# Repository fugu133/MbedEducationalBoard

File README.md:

# Mbed Educational Board
マイコン教育用として開発した基板になります．  
ベースは[mbed LPC1768](https://os.mbed.com/platforms/mbed-LPC1768/)でmbed OSを使ってプロトタイピング開発が可能です.  

サイズが75mm x 55mmの基板に以下の機能が搭載されています．
* タクトスイッチ x4
* アナログボリューム x3
* 完全絶縁のモータドライバ x2
* 6軸IMUセンサ x1
* トランスデューサ x1
* USBコネクタ x1
* GPIO x5 (内2つはI2C)

初学者向けに周辺機器を動かすための[ドライバ](https://github.com/fugu133/MbedEducationalBoard/tree/main/mbed/flib)を用意しているので簡単に扱えるかと思います．

比較的簡単にはんだ付けができるよう一部モジュール基板を使用しています．  
この基板一枚で簡単なロボットも作ることができます！

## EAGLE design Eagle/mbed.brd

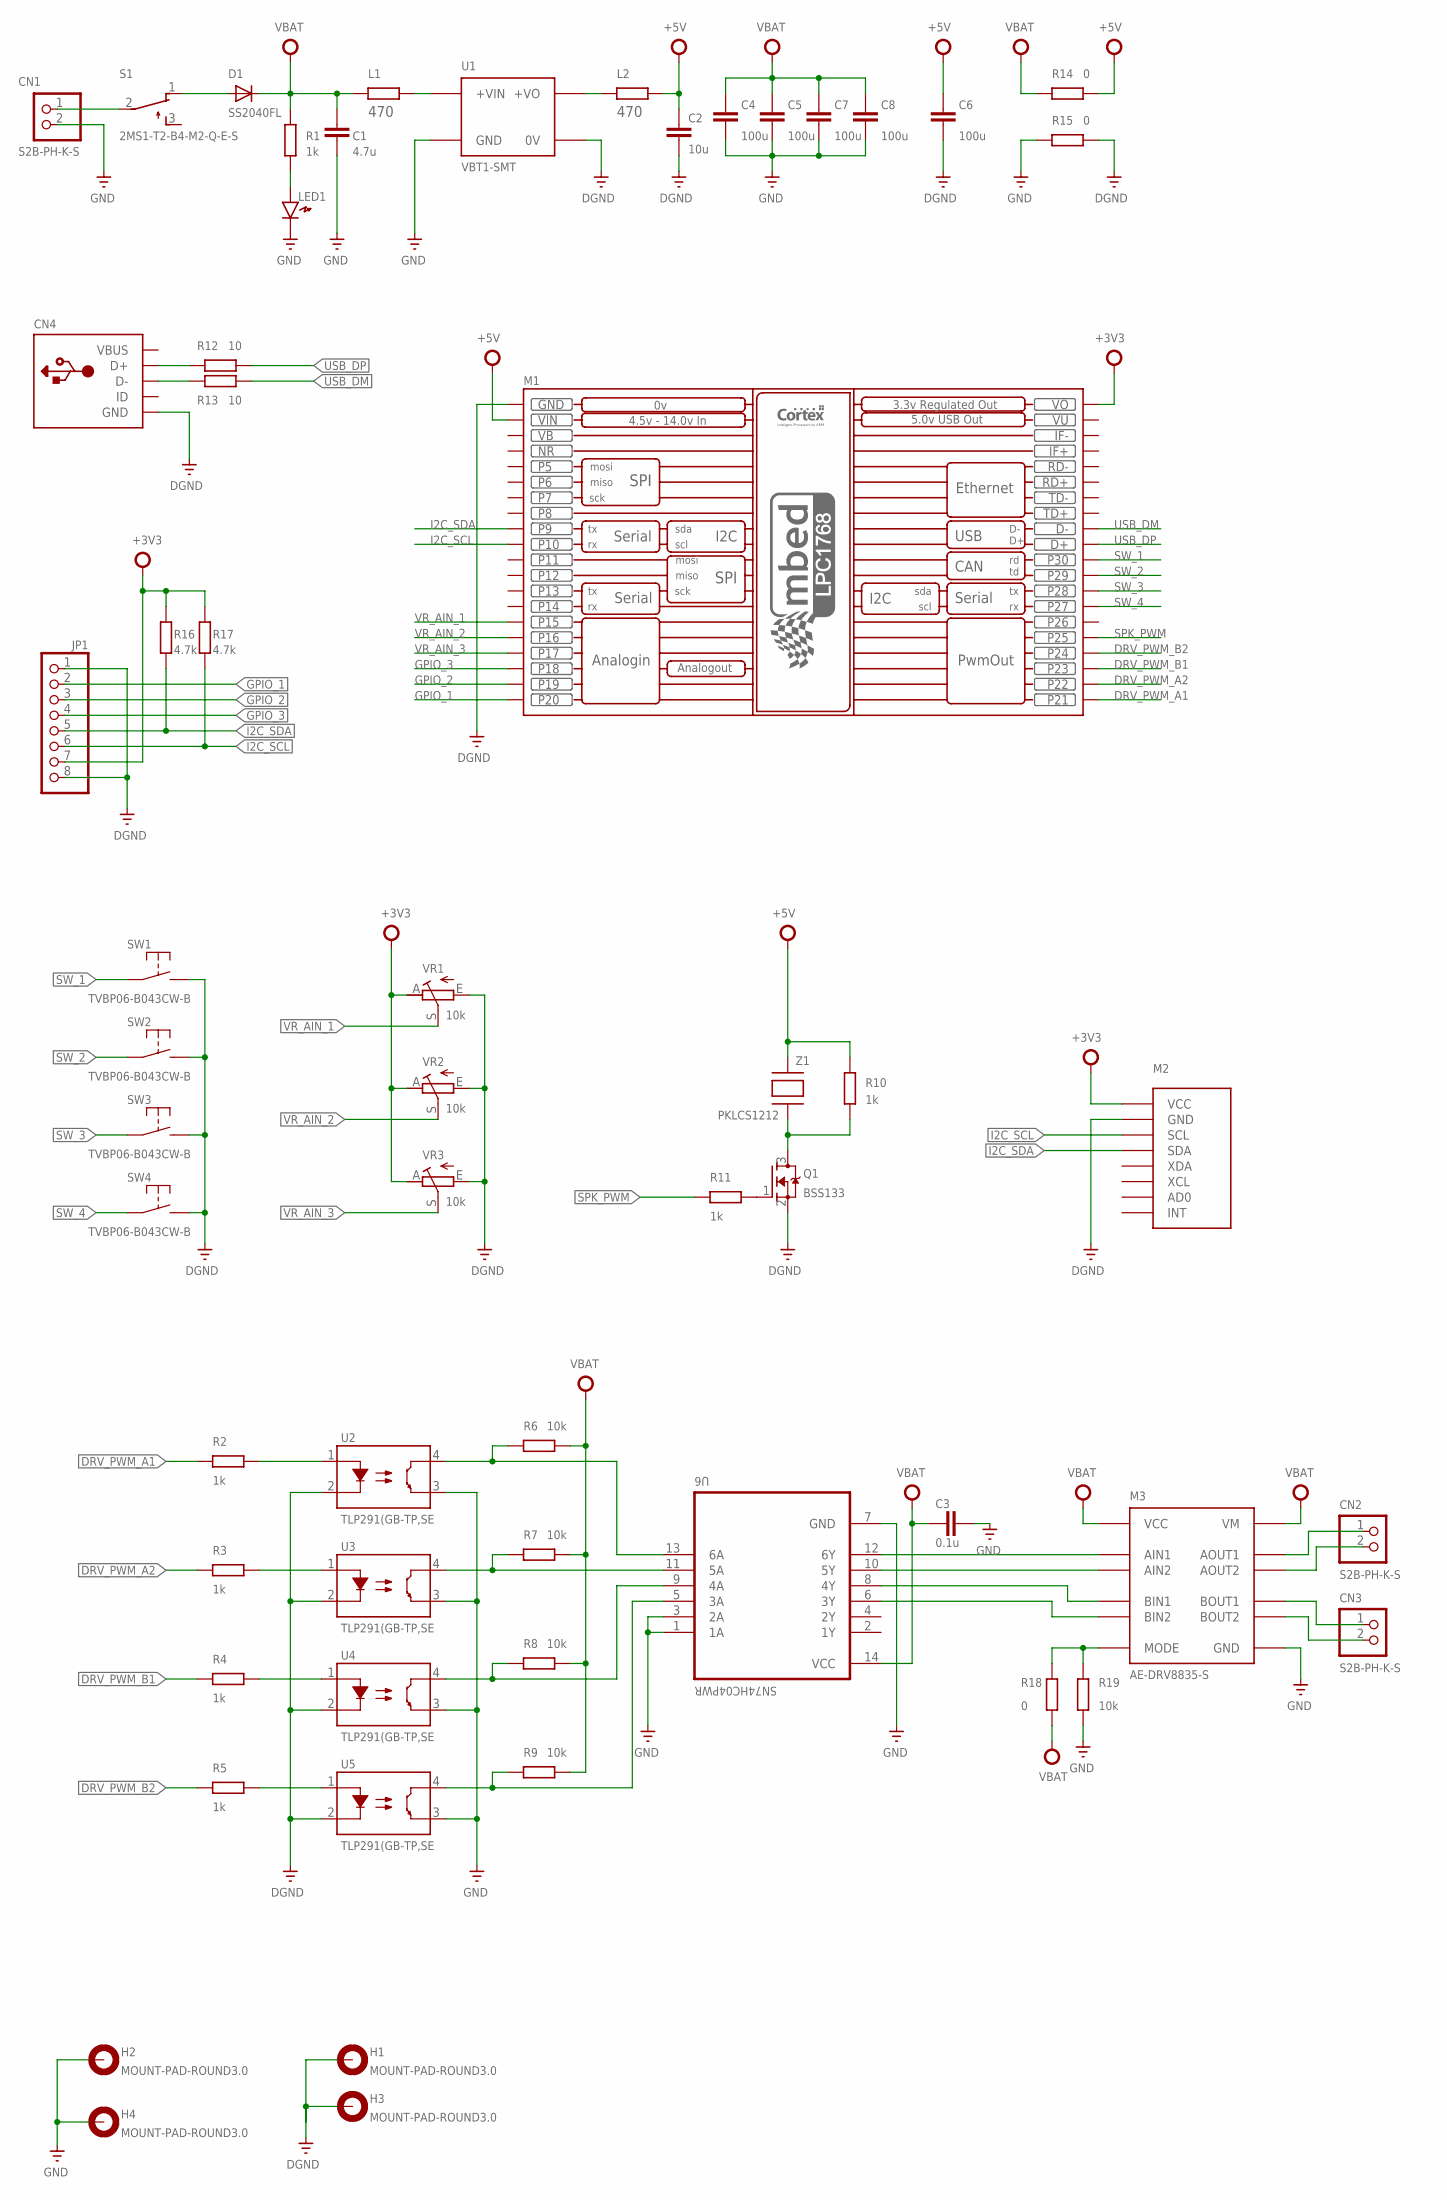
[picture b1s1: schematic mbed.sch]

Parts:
C1: 4.7u; C0603K
C2: 10u; C0603K
C3: 0.1u; C0603K
C4, C5, C6, C7, C8: 100u; C1206K
CN1, CN2, CN3: S2B-PH-K-S; JST-PH-2-THM-RA
CN4: USBMINIB; USB-MINIB
D1: SS2040FL; SOD-123
H1, H2, H3, H4: MOUNT-PAD-ROUND3.0; 3,0-PAD
JP1: PINHD-1X8BIG; 1X08-BIG
L1, L2: 470; R0603
LED1: LED_1608
M1: MBED_NXP_LPC1768; MBED-KIT
M2: MPU6050(GY-521); MPU6050
M3: AE-DRV8835-S; DIL12
Q1: BSS133; SOT23
R1, R2, R3, R4, R5, R10, R11: 1k; R0603
R6, R7, R8, R9, R19: 10k; R0603
R12, R13: 10; R0603
R14, R15, R18: 0; R0603
R16, R17: 4.7k; R0603
S1: 2MS1-T2-B4-M2-Q-E-S; TL3XPO
SW1, SW2, SW3, SW4: TVBP06-B043CW-B; SW1
U1: VBT1-SMT
U2, U3, U4, U5: TLP291(GB-TP,SE; SOIC127P700X220-4N
U6: SN74HC04PWR; SOP65P640X120-14N
VR1, VR2, VR3: 10k; VR-BOURNS
Z1: PKLCS1212

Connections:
+3V3: JP1.7, M1.VOUT (VO), M2.P$1 (VCC), R16.2, R17.2, VR1.A, VR2.A, VR3.A
+5V: C2.1, C6.1, L2.2, M1.VIN, R10.2, R14.1, Z1.P$2
DGND: C2.2, C6.2, CN4.GND, H1.B3,0, H3.B3,0, JP1.1, JP1.8, M1.GND, M2.P$2 (GND), Q1.2 (S), R15.1, SW1.P$2 (S), SW2.P$2 (S), SW3.P$2 (S), SW4.P$2 (S), U1.P$4 (0V), U2.2 (C), U3.2 (C), U4.2 (C), U5.2 (C), VR1.E, VR2.E, VR3.E
DRV_PWM_A1: M1.P$21 (P21), R2.2
DRV_PWM_A2: M1.P$22 (P22), R3.2
DRV_PWM_B1: M1.P$23 (P23), R4.2
DRV_PWM_B2: M1.P$24 (P24), R5.2
GND: C1.2, C3.2, C4.2, C5.2, C7.2, C8.2, CN1.2 (1), H2.B3,0, H4.B3,0, LED1.K, M3.P$6 (GND), R15.2, R19.2, U1.P$1 (GND), U2.3 (EMIT), U3.3 (EMIT), U4.3 (EMIT), U5.3 (EMIT), U6.1 (1A), U6.3 (2A), U6.7 (GND)
GPIO_1: JP1.2, M1.P$20 (P20)
GPIO_2: JP1.3, M1.P$19 (P19)
GPIO_3: JP1.4, M1.P$18 (P18)
I2C_SCL: JP1.6, M1.P$10 (P10), M2.P$3 (SCL), R17.1
I2C_SDA: JP1.5, M1.P$9 (P9), M2.P$4 (SDA), R16.1
unnamed: L2.1, U1.P$5 (+VO)
unnamed: CN1.1 (2), S1.2
unnamed: LED1.A, R1.1
unnamed: Q1.3 (D), R10.1, Z1.P$1
unnamed: Q1.1 (G), R11.1
unnamed: M3.P$8 (BIN1), U6.8 (4Y)
unnamed: M3.P$7 (BIN2), U6.6 (3Y)
unnamed: M3.P$10 (AIN1), U6.12 (6Y)
unnamed: CN2.1 (2), M3.P$2 (AOUT1)
unnamed: CN2.2 (1), M3.P$3 (AOUT2)
unnamed: CN3.1 (2), M3.P$4 (BOUT1)
unnamed: CN3.2 (1), M3.P$5 (BOUT2)
unnamed: R5.1, U5.1 (A)
unnamed: R4.1, U4.1 (A)
unnamed: R3.1, U3.1 (A)
unnamed: R2.1, U2.1 (A)
unnamed: R9.2, U5.4 (COL), U6.5 (3A)
unnamed: R8.1, U4.4 (COL), U6.9 (4A)
unnamed: R7.1, U3.4 (COL), U6.11 (5A)
unnamed: R6.1, U2.4 (COL), U6.13 (6A)
unnamed: D1.A, S1.1 (O)
unnamed: M3.P$11 (MODE), R18.1, R19.1
unnamed: CN4.D-, R13.1
unnamed: CN4.D+, R12.1
unnamed: L1.2, U1.P$2 (+VIN)
unnamed: M3.P$9 (AIN2), U6.10 (5Y)
NR: M1.NR
SPK_PWM: M1.P$25 (P25), R11.2
SW_1: M1.P$30 (P30), SW1.P$1
SW_2: M1.P$29 (P29), SW2.P$1
SW_3: M1.P$28 (P28), SW3.P$1
SW_4: M1.P$27 (P27), SW4.P$1
USB_DM: M1.D-, R13.2
USB_DP: M1.D+, R12.2
VB: M1.VB
VBAT: C1.1, C3.1, C4.1, C5.1, C7.1, C8.1, D1.C, L1.1, M3.P$1 (VM), M3.P$12 (VCC), R1.2, R6.2, R7.2, R8.2, R9.1, R14.2, R18.2, U6.14 (VCC)
VBUS: CN4.VBUS
VR_AIN_1: M1.P$15 (P15), VR1.S
VR_AIN_2: M1.P$16 (P16), VR2.S
VR_AIN_3: M1.P$17 (P17), VR3.S
VU: M1.VU

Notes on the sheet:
SW1
SW2
SW3
SW4
TVBP06-B043CW-B

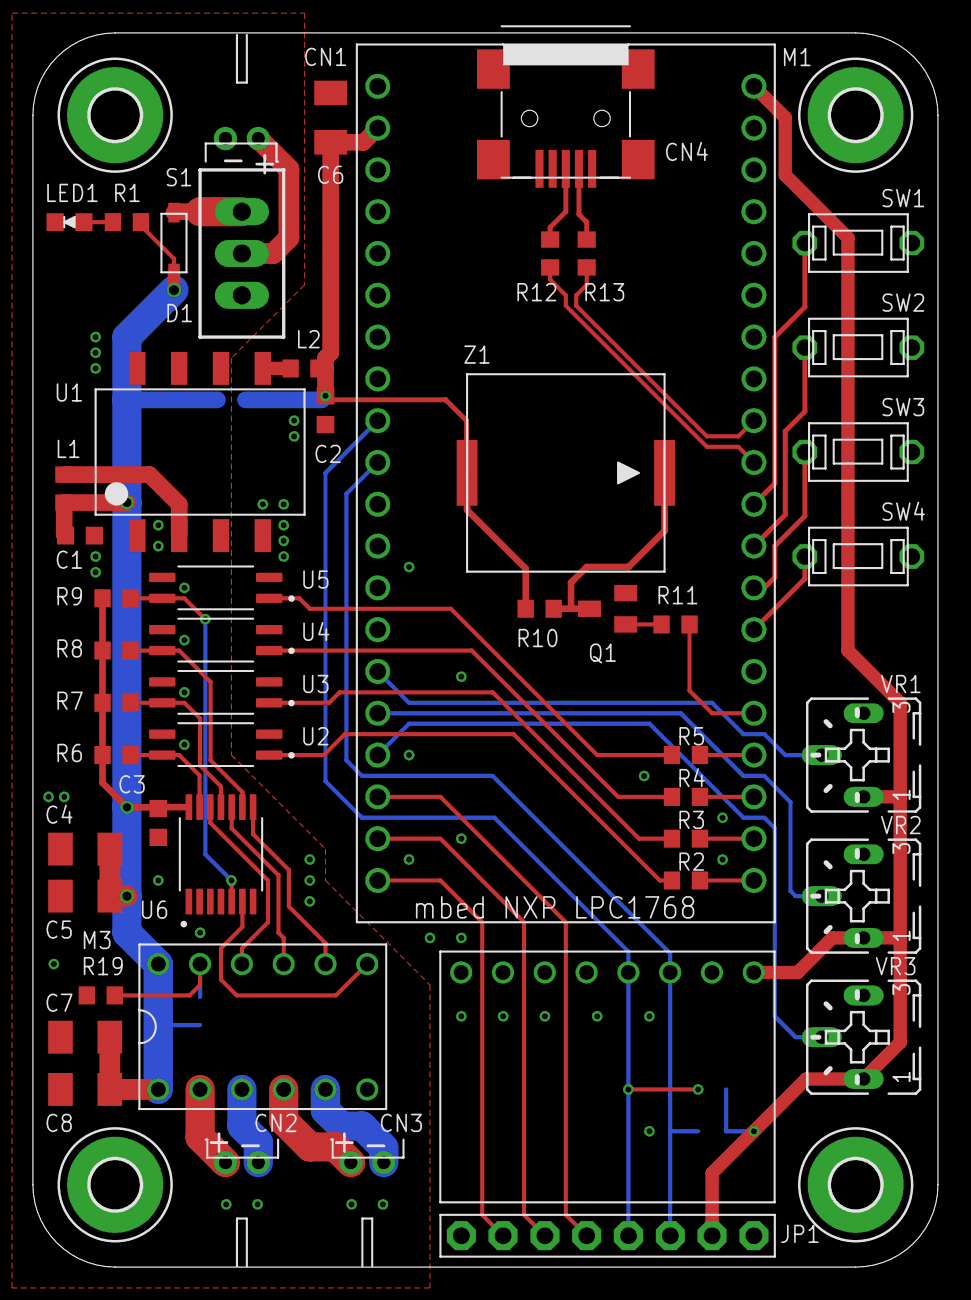
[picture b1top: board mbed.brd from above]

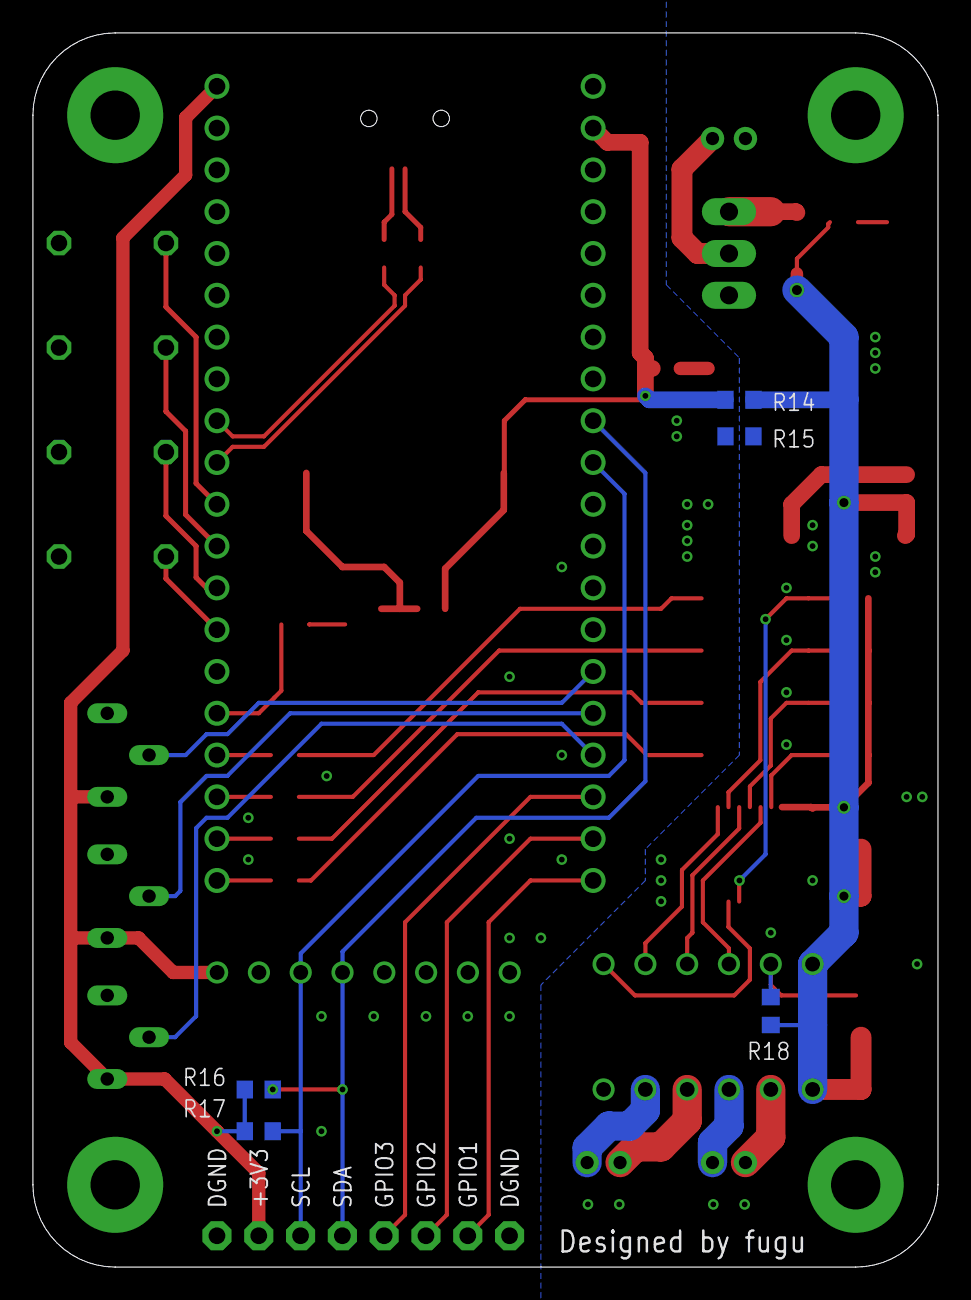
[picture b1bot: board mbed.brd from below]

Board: 2 copper layers, 55.0 x 75.0 mm, 59 parts (5 on the bottom side), 50 nets.

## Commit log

2023-03-02 CADデータを追加
2023-03-02 PCBのガーバーイメージを追加
2023-03-02 ペリフェラルドライバを追加
2023-03-02 文章文章を修正
